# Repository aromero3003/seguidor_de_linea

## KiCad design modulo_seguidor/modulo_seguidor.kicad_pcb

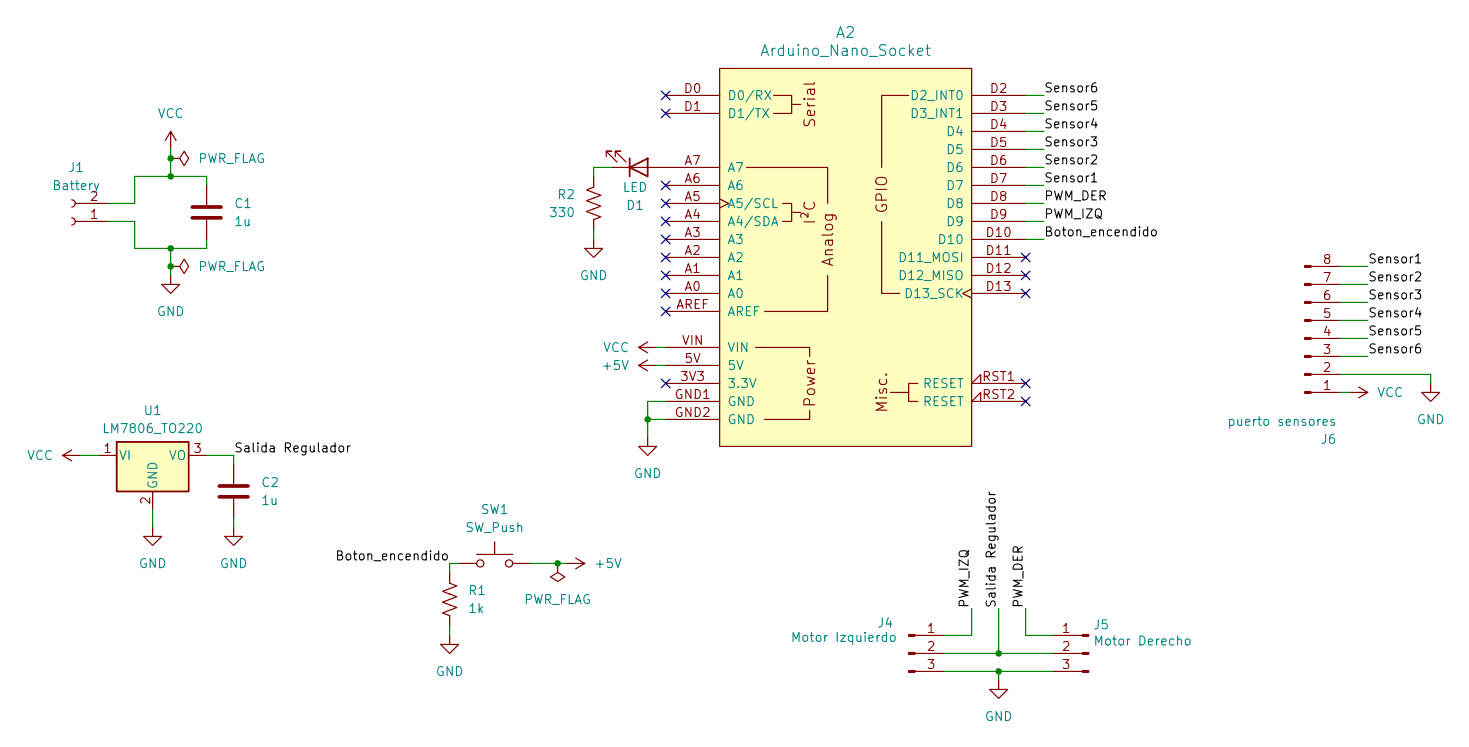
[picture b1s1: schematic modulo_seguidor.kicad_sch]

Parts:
A2: Arduino_Nano_Socket
C1, C2: 1u; C_Disc_D7.0mm_W2.5mm_P5.00mm
D1: LED; LED_D5.0mm
J1: Battery; Molex_KK-254_AE-6410-02A_1x02_P2.54mm_Vertical
J4: Motor Izquierdo; PinHeader_1x03_P2.54mm_Vertical
J5: Motor Derecho; PinHeader_1x03_P2.54mm_Vertical
J6: puerto sensores; PinHeader_1x08_P2.54mm_Vertical
R1: 1k; R_Axial_DIN0411_L9.9mm_D3.6mm_P12.70mm_Horizontal
R2: 330; R_Axial_DIN0411_L9.9mm_D3.6mm_P12.70mm_Horizontal
SW1: SW_Push; SW_PUSH_6mm
U1: LM7806_TO220; TO-220-3_Vertical

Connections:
+5V: A2.5V, SW1.1
/Boton_encendido: A2.D10, R1.1, SW1.2
/PWM_DER: A2.D8, J5.1
/PWM_IZQ: A2.D9, J4.1
/Salida Regulador: C2.1, J4.2, J5.2, U1.3 (VO)
/Sensor1: A2.D7, J6.8
/Sensor2: A2.D6, J6.7
/Sensor3: A2.D5, J6.6
/Sensor4: A2.D4, J6.5
/Sensor5: A2.D3 (D3_INT1), J6.4
/Sensor6: A2.D2 (D2_INT0), J6.3
GND: A2.GND1 (GND), A2.GND2 (GND), C1.2, C2.2, J1.1, J4.3, J5.3, J6.2, R1.2, R2.2, U1.2 (GND)
unnamed: A2.A7, D1.2 (A)
unnamed: D1.1 (K), R2.1
VCC: A2.VIN, C1.1, J1.2, J6.1, U1.1 (VI)

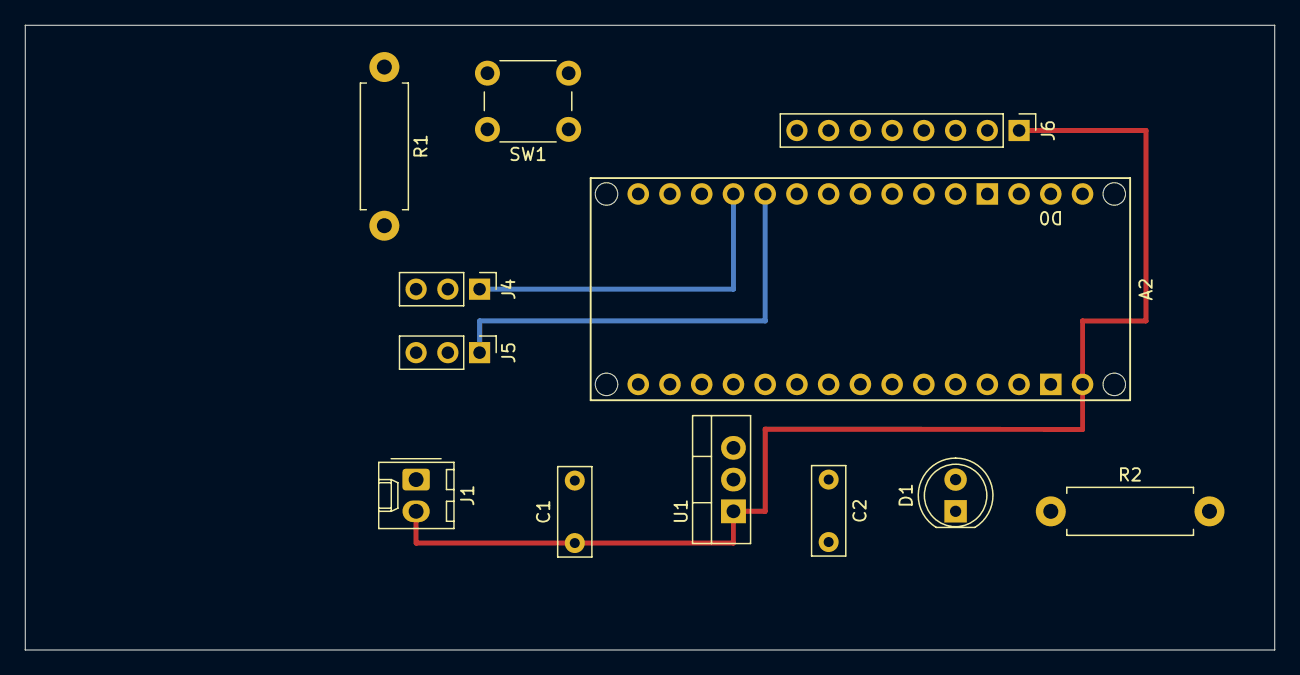
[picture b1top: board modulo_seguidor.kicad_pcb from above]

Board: 12 copper layers, 100.0 x 50.0 mm, 12 parts (0 on the bottom side), 15 nets.

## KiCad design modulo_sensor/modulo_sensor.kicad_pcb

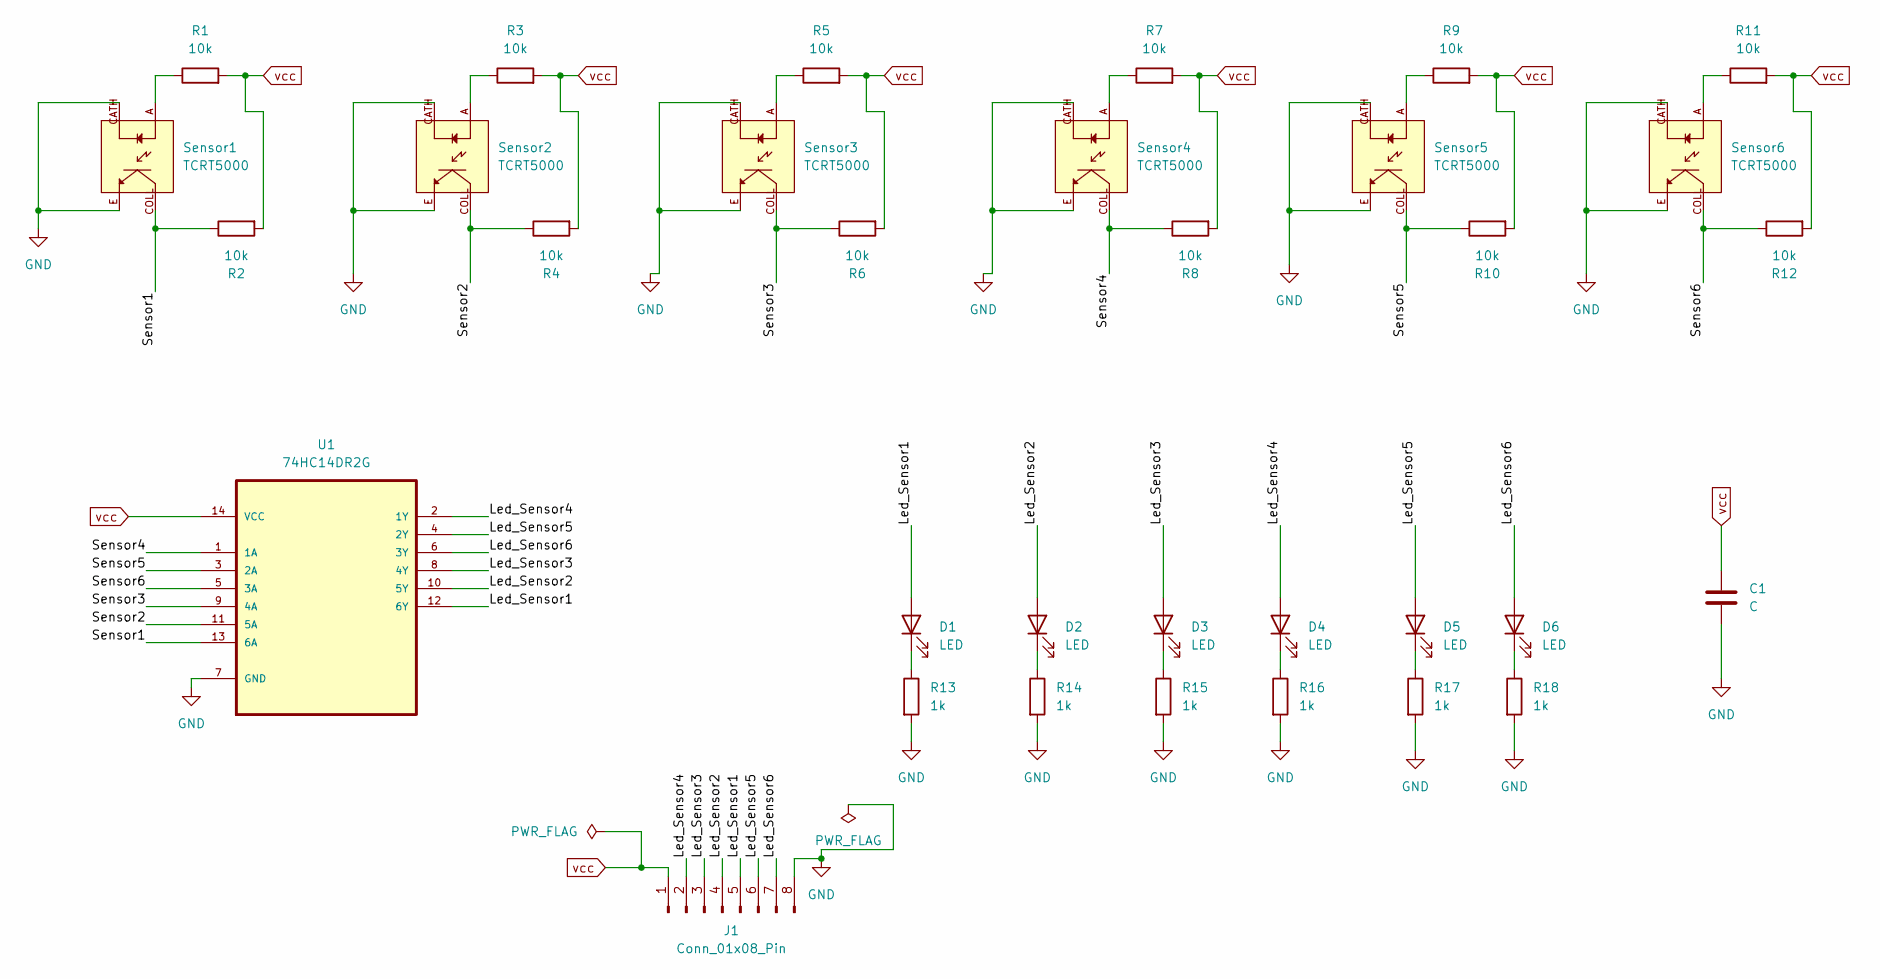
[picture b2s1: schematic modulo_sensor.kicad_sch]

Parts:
C1: C; C_Disc_D3.0mm_W1.6mm_P2.50mm
D1, D2, D3, D4, D5, D6: LED; LED_1206_3216Metric_Pad1.42x1.75mm_HandSolder
J1: Conn_01x08_Pin; PinHeader_1x08_P1.27mm_Horizontal
R1, R2, R3, R4, R5, R6, R7, R8, R9, R10, R11, R12: 10k; R_0805_2012Metric_Pad1.20x1.40mm_HandSolder
R13, R14, R15, R16, R17, R18: 1k; R_0805_2012Metric_Pad1.20x1.40mm_HandSolder
Sensor1, Sensor2, Sensor3, Sensor4, Sensor5, Sensor6: TCRT5000; OPTO_TCRT5000; PARTREV 1.7
U1: 74HC14DR2G; DIP-14_W7.62mm_Socket; MPN 74HC14DR2G

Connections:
/Led_Sensor1: D1.2 (A), J1.5, U1.12 (6Y)
/Led_Sensor2: D2.2 (A), J1.4, U1.10 (5Y)
/Led_Sensor3: D3.2 (A), J1.3, U1.8 (4Y)
/Led_Sensor4: D4.2 (A), J1.2, U1.2 (1Y)
/Led_Sensor5: D5.2 (A), J1.6, U1.4 (2Y)
/Led_Sensor6: D6.2 (A), J1.7, U1.6 (3Y)
/Sensor1: R2.1, Sensor1.COLL, U1.13 (6A)
/Sensor2: R4.1, Sensor2.COLL, U1.11 (5A)
/Sensor3: R6.1, Sensor3.COLL, U1.9 (4A)
/Sensor4: R8.1, Sensor4.COLL, U1.1 (1A)
/Sensor5: R10.1, Sensor5.COLL, U1.3 (2A)
/Sensor6: R12.1, Sensor6.COLL, U1.5 (3A)
GND: C1.2, J1.8, R13.2, R14.2, R15.2, R16.2, R17.2, R18.2, Sensor1.CATH, Sensor1.E, Sensor2.CATH, Sensor2.E, Sensor3.CATH, Sensor3.E, Sensor4.CATH, Sensor4.E, Sensor5.CATH, Sensor5.E, Sensor6.CATH, Sensor6.E, U1.7 (GND)
unnamed: D1.1 (K), R13.1
unnamed: D2.1 (K), R14.1
unnamed: D3.1 (K), R15.1
unnamed: D4.1 (K), R16.1
unnamed: D5.1 (K), R17.1
unnamed: D6.1 (K), R18.1
unnamed: R1.1, Sensor1.A
unnamed: R3.1, Sensor2.A
unnamed: R5.1, Sensor3.A
unnamed: R7.1, Sensor4.A
unnamed: R9.1, Sensor5.A
unnamed: R11.1, Sensor6.A
vcc: C1.1, J1.1, R1.2, R2.2, R3.2, R4.2, R5.2, R6.2, R7.2, R8.2, R9.2, R10.2, R11.2, R12.2, U1.14 (VCC)

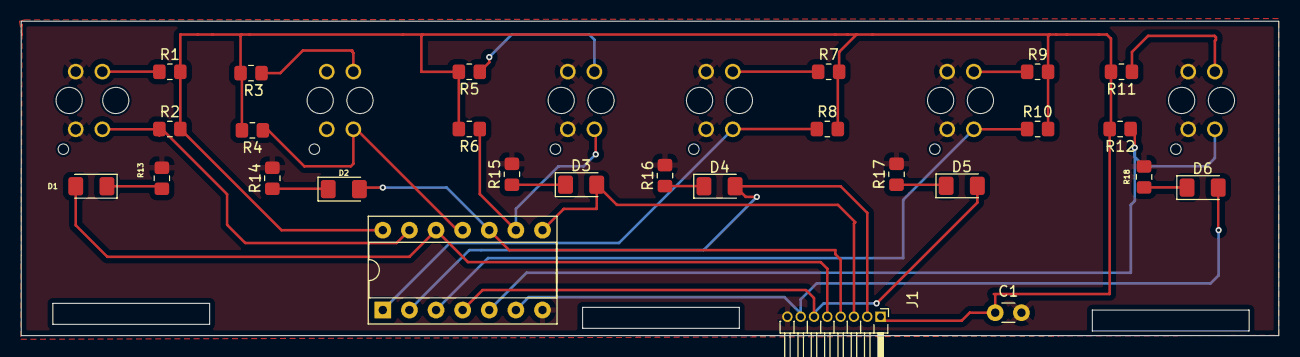
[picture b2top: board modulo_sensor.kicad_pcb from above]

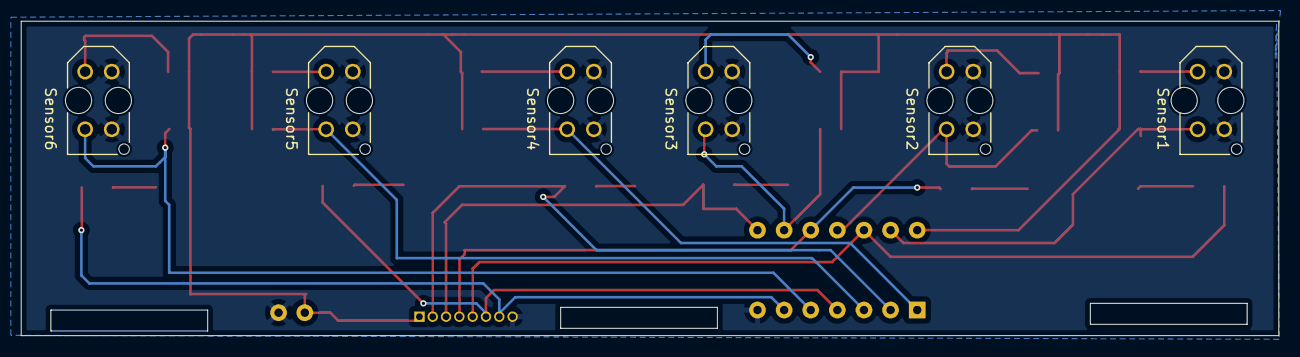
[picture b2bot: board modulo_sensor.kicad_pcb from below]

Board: 2 copper layers, 120.0 x 30.0 mm, 33 parts (6 on the bottom side), 26 nets.

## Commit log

2024-10-01 feat: Placa doble faz
    Placa 120x30mm doble faz
2024-10-13 refactor: Muevo los pines al lado del arduino nano
    Reorganizo las conexiones pero nos ahorramos los cables de los sensores
2024-10-13 docs: Agrego la vista previa y la vista del pcb del modulo seguidor
